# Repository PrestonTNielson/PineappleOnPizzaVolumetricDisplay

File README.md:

# Volumetric-Display-Template-2026
Template for the IEEE Fall 2026 Project Volumetric display

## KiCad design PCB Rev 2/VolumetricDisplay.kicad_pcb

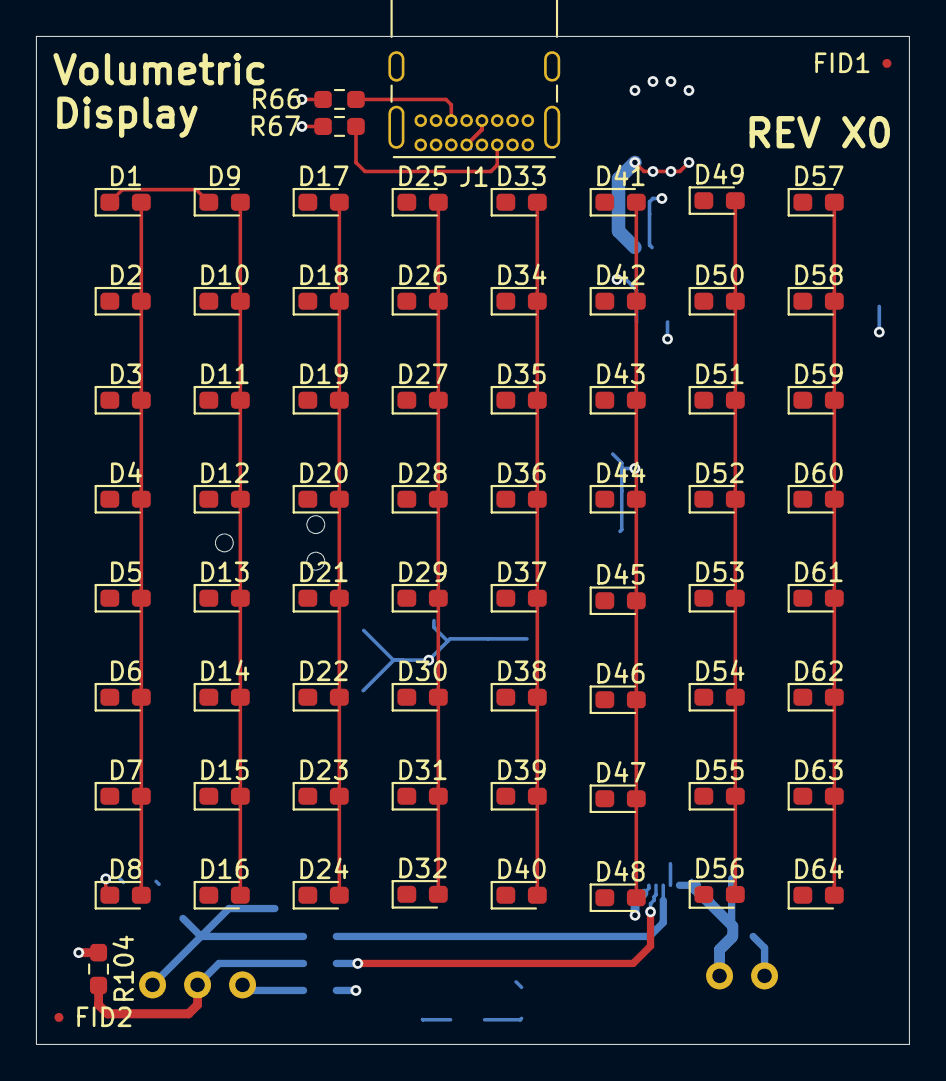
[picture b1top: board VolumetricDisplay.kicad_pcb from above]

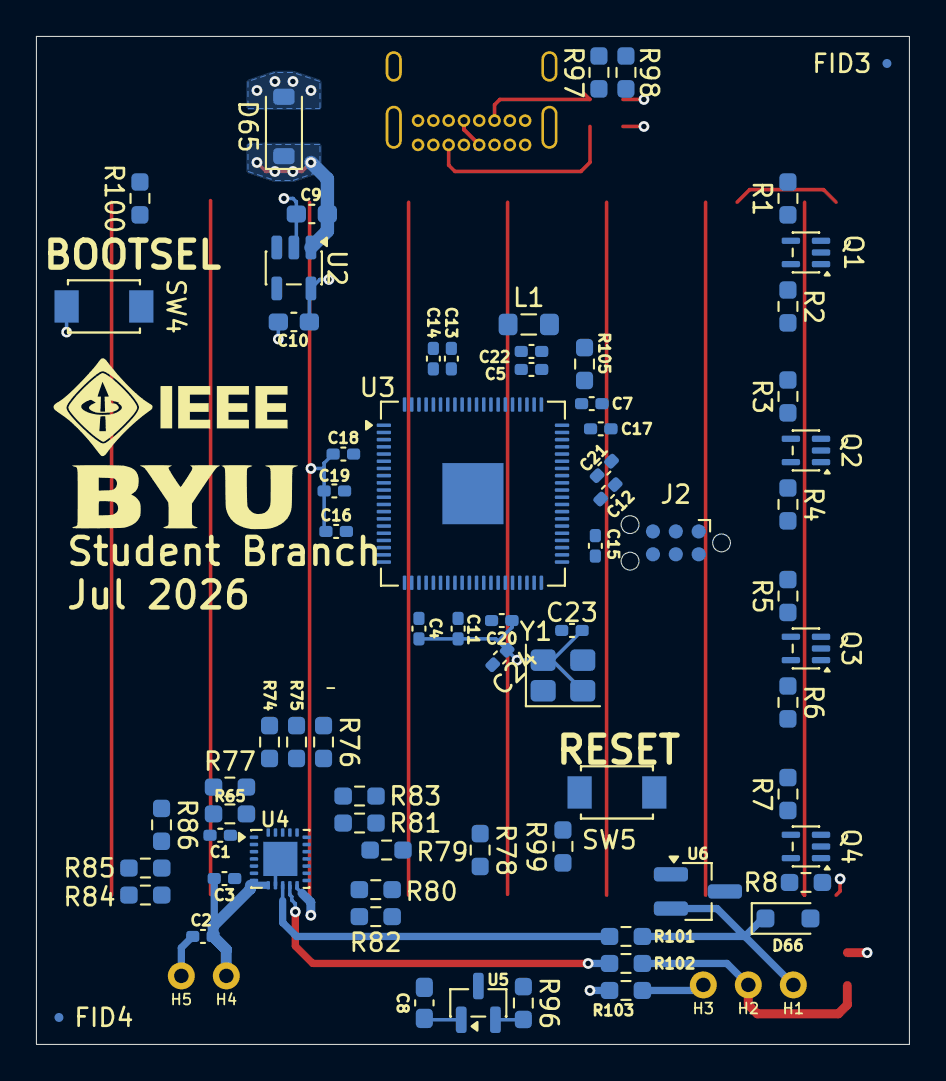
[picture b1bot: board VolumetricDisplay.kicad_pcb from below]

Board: 4 copper layers, 48.5 x 56.0 mm, 147 parts (77 on the bottom side), 86 nets.

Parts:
C1, C3: 0.1uF; C_0402_1005Metric_Pad0.74x0.62mm_HandSolder
C2: 1uF; C_0402_1005Metric_Pad0.74x0.62mm_HandSolder
C4, C11, C12, C13, C14, C15, C16, C17, C18, C19, C20, C21: 100nF; C_0402_1005Metric_Pad0.74x0.62mm_HandSolder
C5, C7, C22: 4.7uF; C_0402_1005Metric_Pad0.74x0.62mm_HandSolder
C8: 0.1uF; C_0603_1608Metric_Pad1.08x0.95mm_HandSolder
C9, C10: 1uF; C_0603_1608Metric_Pad1.08x0.95mm_HandSolder
C23, C24: 15pF; C_0402_1005Metric_Pad0.74x0.62mm_HandSolder
D1, D2, D3, D4, D5, D6, D7, D8, D9, D10, D11, D12, D13, D14, D15, D16, D17, D18, D19, D20, D21, D22, D23, D24, D25, D26, D27, D28, D29, D30, D31, D32, D33, D34, D35, D36, D37, D38, D39, D40, D41, D42, D43, D44, D45, D46, D47, D48, D49, D50, D51, D52, D53, D54, D55, D56, D57, D58, D59, D60, D61, D62, D63, D64: LED; LED_0603_1608Metric_Pad1.05x0.95mm_HandSolder
D65: MBR0560; D_SOD-123
D66: 1N4148WT; D_SOD-323_HandSoldering
FID1, FID2, FID3, FID4: Fiducial; Fiducial_0.5mm_Mask1mm
H1, H2, H3, H4, H5: MountingHole_Pad; 28AWG Pad
J1: USB_C_Receptacle_USB2.0_16P; USB_C_Receptacle_GCT_USB4085
J2: Conn_ARM_SWD_TagConnect_TC2030; Tag-Connect_TC2030-IDC-NL_2x03_P1.27mm_Vertical
L1: 3.3uH; L_0805_2012Metric_Pad1.05x1.20mm_HandSolder
Q1, Q2, Q3, Q4: DMN32D2LDF; SOT-353_SC-70-5
R1, R2, R3, R4, R5, R6, R7, R8: 50; R_0603_1608Metric_Pad0.98x0.95mm_HandSolder
R65, R99, R100: 10K; R_0603_1608Metric_Pad0.98x0.95mm_HandSolder
R66, R67: 5.1K; R_0603_1608Metric_Pad0.98x0.95mm_HandSolder
R74, R75, R76, R77, R78, R79, R80, R81, R82, R83, R84, R85, R86, R96, R101, R102, R103, R104: 0; R_0603_1608Metric_Pad0.98x0.95mm_HandSolder
R97, R98: 50K; R_0603_1608Metric_Pad0.98x0.95mm_HandSolder
R105: 33; R_0603_1608Metric_Pad0.98x0.95mm_HandSolder
SW4, SW5: TS-1088-AR02016; SW_TS-1088-AR02016
U2: NCP718xSN330; SOT-23-5
U3: RP2354B; QFN-80-1EP_10x10mm_P0.4mm_EP3.4x3.4mm
U4: DRV8311S; Texas_RRW0024A_WQFN-24-1EP_3x3mm_P0.4mm_EP1.9x1.9mm
U5: DRV5055A1xDBZxQ1; SOT-23
U6: SOT-23_Handsoldering
Y1: Abracon ABM8-272-T3; Crystal_SMD_Abracon_ABM8G-4Pin_3.2x2.5mm

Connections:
3V3: C4.1, C5.1, C8.2, C10.1, C11.1, C12.1, C13.1, C14.1, C15.1, C16.1, C17.1, C18.1, J2.1 (VCC), R99.2, R100.2, R105.1, U2.5 (OUT), U3.5 (IOVDD), U3.15 (IOVDD), U3.24 (IOVDD), U3.29 (IOVDD), U3.41 (IOVDD), U3.50 (IOVDD), U3.59 (ADC_AVDD), U3.60 (IOVDD), U3.64 (VREG_VIN), U3.68 (USB_OTP_VDD), U3.69 (QSPI_IOVDD), U3.76 (IOVDD), U5.1 (VCC)
5V: C2.1, C3.2, C9.1, D65.1 (K), H4.1 (1_1), R65.1, R104.1, U2.1 (IN), U2.3 (EN), U4.7 (VIN_AVDD), U4.8 (VM), U4.17 (AVDD)
+1V1: C19.1, C20.1, C21.1, C22.1, L1.1, U3.10 (DVDD), U3.32 (DVDD), U3.51 (DVDD), U3.65 (VREG_FB)
/MCU/QSPI_CS: R100.1, SW4.2, U3.75 (~QSPI_SS)
/MCU/VBUS: D65.2 (A), J1.A4 (VBUS), J1.A9 (VBUS), J1.B4 (VBUS), J1.B9 (VBUS)
D_N: J1.A7 (D-), J1.B7 (D-), U3.66 (USB_DM)
D_P: J1.A6 (D+), J1.B6 (D+), U3.67 (USB_DP)
FET0: Q1.4 (D2), R1.1
FET1: Q1.5 (D1), R2.1
FET2: Q2.4 (D2), R3.1
FET3: Q2.5 (D1), R4.1
FET4: Q3.4 (D2), R5.1
FET5: Q3.5 (D1), R6.1
FET6: Q4.4 (D2), R7.1
FET7: Q4.5 (D1), R8.1
GND: C1.1, C2.2, C4.2, C5.2, C7.2, C8.1, C9.2, C10.2, C11.2, C12.2, C13.2, C14.2, C15.2, C16.2, C17.2, C18.2, C19.2, C20.2, C21.2, C22.2, C23.1, C24.1, D41.2 (A), D42.2 (A), D43.2 (A), D44.2 (A), D45.2 (A), D46.2 (A), D47.2 (A), D48.2 (A), D66.2 (A), H5.1 (1_1), J1.A1 (GND), J1.A12 (GND), J1.B1 (GND), J1.B12 (GND), J2.5 (GND), Q1.2 (S), Q2.2 (S), Q3.2 (S), Q4.2 (S), R66.1, R67.1, R98.2, SW4.1, SW5.1, U2.2 (GND), U3.62 (VREG_PGND), U3.81 (GND), U4.9 (PGND), U4.16 (AGND), U4.25 (PGND), U5.3 (GND), U6.3 (Drain), Y1.2 (G), Y1.4 (G)
HALL: R96.2, U5.2 (OUT)
LED0: D1.2 (A), D2.2 (A), D3.2 (A), D4.2 (A), D5.2 (A), D6.2 (A), D7.2 (A), D8.2 (A), U3.12 (GPIO13)
LED1: D9.2 (A), D10.2 (A), D11.2 (A), D12.2 (A), D13.2 (A), D14.2 (A), D15.2 (A), D16.2 (A), U3.13 (GPIO14)
LED2: D17.2 (A), D18.2 (A), D19.2 (A), D20.2 (A), D21.2 (A), D22.2 (A), D23.2 (A), D24.2 (A), U3.14 (GPIO15)
LED3: D25.2 (A), D26.2 (A), D27.2 (A), D28.2 (A), D29.2 (A), D30.2 (A), D31.2 (A), D32.2 (A), U3.16 (GPIO16)
LED4: D33.2 (A), D34.2 (A), D35.2 (A), D36.2 (A), D37.2 (A), D38.2 (A), D39.2 (A), D40.2 (A), U3.17 (GPIO17)
LED6: D49.2 (A), D50.2 (A), D51.2 (A), D52.2 (A), D53.2 (A), D54.2 (A), D55.2 (A), D56.2 (A), U3.19 (GPIO19)
LED7: D57.2 (A), D58.2 (A), D59.2 (A), D60.2 (A), D61.2 (A), D62.2 (A), D63.2 (A), D64.2 (A), U3.20 (GPIO20)
LED8: Q1.3 (G2), U3.36 (GPIO28)
LED9: Q1.1 (G1), U3.28 (GPIO27)
LED10: Q2.3 (G2), U3.27 (GPIO26)
LED11: Q2.1 (G1), U3.26 (GPIO25)
LED12: Q3.3 (G2), U3.25 (GPIO24)
LED13: Q3.1 (G1), U3.23 (GPIO23)
LED14: Q4.1 (G1), U3.22 (GPIO22)
LED15: Q4.3 (G2), U3.21 (GPIO21)
MTR_FET: R78.2, U4.15 (INHA), U6.1 (Gate)
MTR_ISENA: R84.2, U4.5 (SOA)
MTR_ISENB: R85.2, U4.4 (SOB)
MTR_ISENC: R86.2, U4.3 (SOC)
MTR_nFAULT: R65.2, U4.1 (~FAULT)
unnamed: D1.1 (K), D9.1 (K), D17.1 (K), D25.1 (K), D33.1 (K), D41.1 (K), D49.1 (K), D57.1 (K), R1.2
unnamed: D2.1 (K), D10.1 (K), D18.1 (K), D26.1 (K), D34.1 (K), D42.1 (K), D50.1 (K), D58.1 (K), R2.2
unnamed: D3.1 (K), D11.1 (K), D19.1 (K), D27.1 (K), D35.1 (K), D43.1 (K), D51.1 (K), D59.1 (K), R3.2
unnamed: D4.1 (K), D12.1 (K), D20.1 (K), D28.1 (K), D36.1 (K), D44.1 (K), D52.1 (K), D60.1 (K), R4.2
unnamed: D5.1 (K), D13.1 (K), D21.1 (K), D29.1 (K), D37.1 (K), D45.1 (K), D53.1 (K), D61.1 (K), R5.2
unnamed: D6.1 (K), D14.1 (K), D22.1 (K), D30.1 (K), D38.1 (K), D46.1 (K), D54.1 (K), D62.1 (K), R6.2
unnamed: D7.1 (K), D15.1 (K), D23.1 (K), D31.1 (K), D39.1 (K), D47.1 (K), D55.1 (K), D63.1 (K), R7.2
unnamed: D8.1 (K), D16.1 (K), D24.1 (K), D32.1 (K), D40.1 (K), D48.1 (K), D56.1 (K), D64.1 (K), R8.2
unnamed: D66.1 (K), H1.1 (1_1), R101.1, U6.2 (Source)
unnamed: H2.1 (1_1), R102.1, R104.2
unnamed: H3.1 (1_1), R103.1
unnamed: J1.A5 (CC1), R67.2
unnamed: J1.B5 (CC2), R66.2
unnamed: R86.1, U3.77 (GPIO0)
unnamed: R77.1, U3.78 (GPIO1)
unnamed: R74.1, U3.79 (GPIO2)
unnamed: R75.1, U3.80 (GPIO3)
unnamed: R76.1, U3.1 (GPIO4)
unnamed: R78.1, U3.2 (GPIO5)
unnamed: R79.1, U3.3 (GPIO6)
unnamed: R80.1, U3.4 (GPIO7)
unnamed: R81.1, U3.6 (GPIO8)
unnamed: R82.1, U3.7 (GPIO9)
unnamed: R83.1, U3.8 (GPIO10)
unnamed: R84.1, U3.9 (GPIO11)
unnamed: R85.1, U3.11 (GPIO12)
unnamed: R96.1, U3.52 (GPIO41/ADC1)
unnamed: C7.1, R105.2, U3.61 (VREG_AVDD)
unnamed: L1.2, U3.63 (VREG_LX)
unnamed: C24.2, U3.30 (XIN), Y1.1
unnamed: C23.2, U3.31 (XOUT), Y1.3
unnamed: C3.1, U4.6 (CP)
unnamed: C1.2, U4.2 (CSAREF)
unnamed: R101.2, U4.10 (OUTA)
unnamed: R102.2, U4.11 (OUTB)
unnamed: R103.2, U4.12 (OUTC)
PWM_A_L: R79.2, U4.18 (INLA)
PWM_B_H: R80.2, U4.14 (INHB)
PWM_B_L: R81.2, U4.19 (INLB)
PWM_C_H: R82.2, U4.13 (INHC)
PWM_C_L: R83.2, U4.20 (INLC)
SPI_MISO: R76.2, U4.21 (SDO)
SPI_MOSI: R75.2, U4.22 (SDI)
SPI_MTR_CS: R77.2, U4.24 (~SCS)
SPI_SCLK: R74.2, U4.23 (SCLK)
SWCLK: J2.4 (SWCLK), U3.33 (SWCLK)
SWDIO: J2.2 (SWDIO), U3.34 (SWDIO)
USB_DET: R98.1, U3.49 (GPIO40/ADC0)
nRST: J2.3 (~RESET), R99.1, SW5.2, U3.35 (RUN)
